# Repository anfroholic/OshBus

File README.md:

# OshBus
Open source messaging protocol for embeded systems

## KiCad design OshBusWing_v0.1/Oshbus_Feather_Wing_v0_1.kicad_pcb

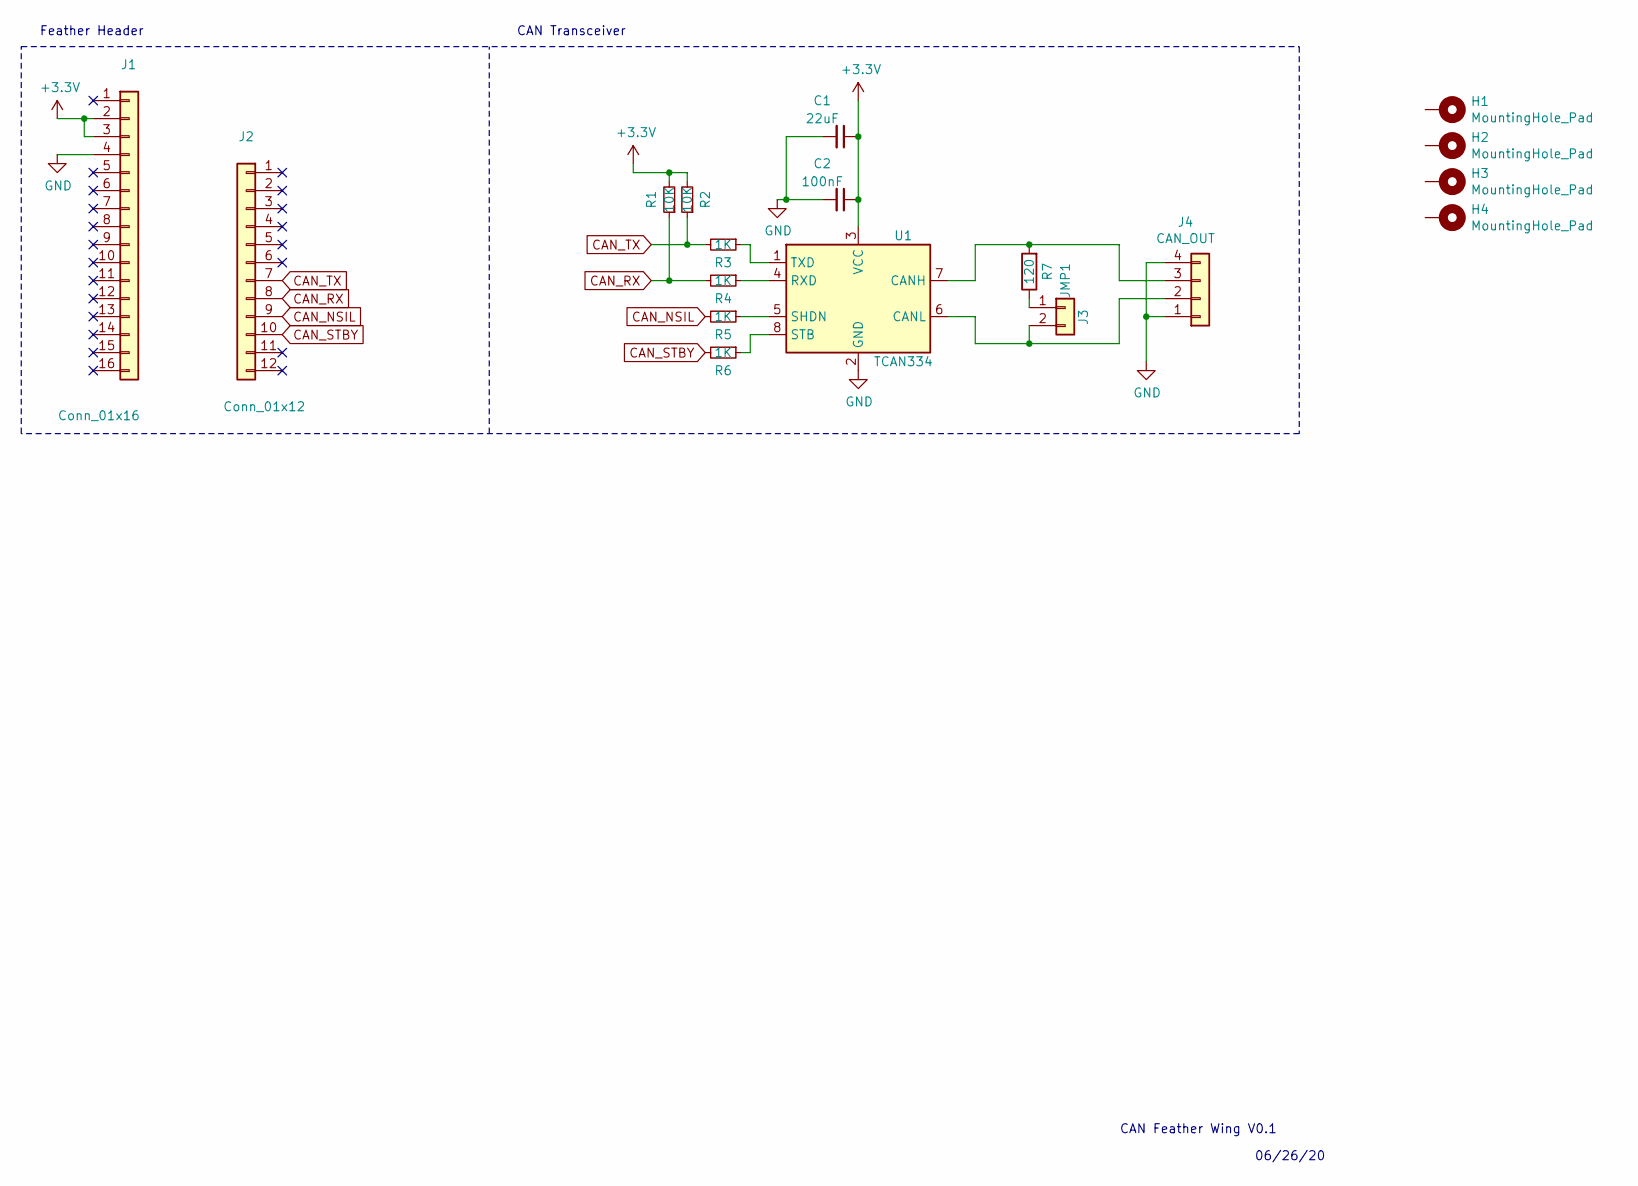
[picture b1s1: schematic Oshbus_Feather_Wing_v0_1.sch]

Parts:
C1: 22uF; C_0603_1608Metric_Pad1.05x0.95mm_HandSolder
C2: 100nF; C_0603_1608Metric_Pad1.05x0.95mm_HandSolder
H1, H2, H3, H4: MountingHole_Pad; MountingHole_2.5mm
J1: Conn_01x16; PinSocket_1x16_P2.54mm_Vertical
J2: Conn_01x12; PinSocket_1x12_P2.54mm_Vertical
J3: JMP1; PinHeader_1x02_P2.54mm_Vertical
J4: CAN_OUT; JST_PH_B4B-PH-K_1x04_P2.00mm_Vertical
R1, R2: 10K; R_0603_1608Metric_Pad1.05x0.95mm_HandSolder
R3, R4, R5, R6: 1K; R_0603_1608Metric_Pad1.05x0.95mm_HandSolder
R7: 120; R_1206_3216Metric_Pad1.42x1.75mm_HandSolder
U1: TCAN334; SOT-23-8_Handsoldering

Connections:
+3V3: C1.1, C2.1, J1.2, J1.3, R1.2, R2.2, U1.3 (VCC)
CAN_NSIL: J2.9, R5.2
CAN_RX: J2.8, R1.1, R4.2
CAN_STBY: J2.10, R6.2
CAN_TX: J2.7, R2.1, R3.2
GND: C1.2, C2.2, J1.4, J4.1, J4.4, U1.2 (GND)
unnamed: J3.1, R7.1
unnamed: J3.2, J4.2, U1.6 (CANL)
unnamed: J4.3, R7.2, U1.7 (CANH)
unnamed: R3.1, U1.1 (TXD)
unnamed: R4.1, U1.4 (RXD)
unnamed: R5.1, U1.5 (SHDN)
unnamed: R6.1, U1.8 (STB)

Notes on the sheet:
Feather Header
CAN Transceiver
CAN Feather Wing V0.1
06/26/20

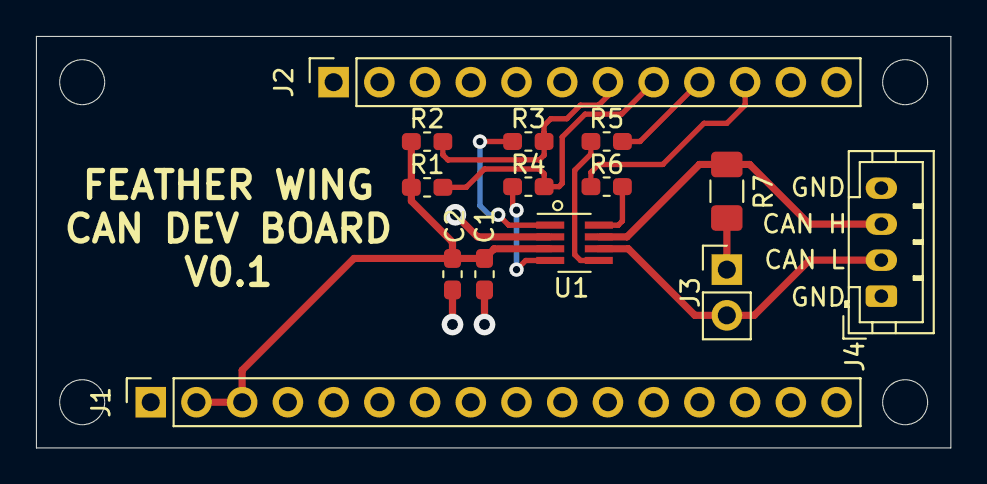
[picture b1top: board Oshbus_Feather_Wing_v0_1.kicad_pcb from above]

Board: 2 copper layers, 50.8 x 22.9 mm, 18 parts (0 on the bottom side), 13 nets.

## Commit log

2020-06-28 Update OshBusExample.json
    added firmware versioning
2020-08-04 Removed Parent and Child Terminology
    cause we overthought some things.
2020-08-06 Create a dictionary example and instructions on how to hash
    This is a work in progress, but the hashing instructions can be useful so I wanted to get an initial commit up before work continues.
